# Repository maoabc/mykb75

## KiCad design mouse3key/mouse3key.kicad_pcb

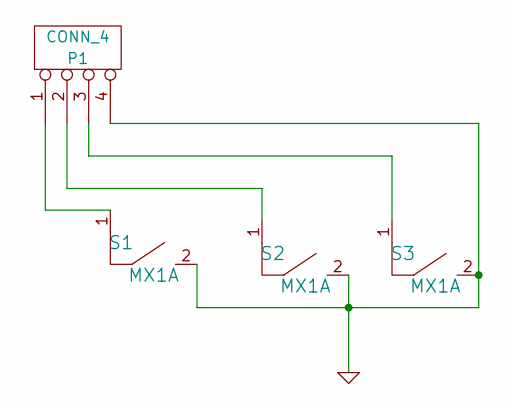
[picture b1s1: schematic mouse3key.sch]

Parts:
P1: CONN_4; connector-ffc-4p
S1, S2, S3: MX1A

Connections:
GND: P1.4, S1.2, S2.2, S3.2
unnamed: P1.1, S1.1
unnamed: P1.2, S2.1
unnamed: P1.3, S3.1

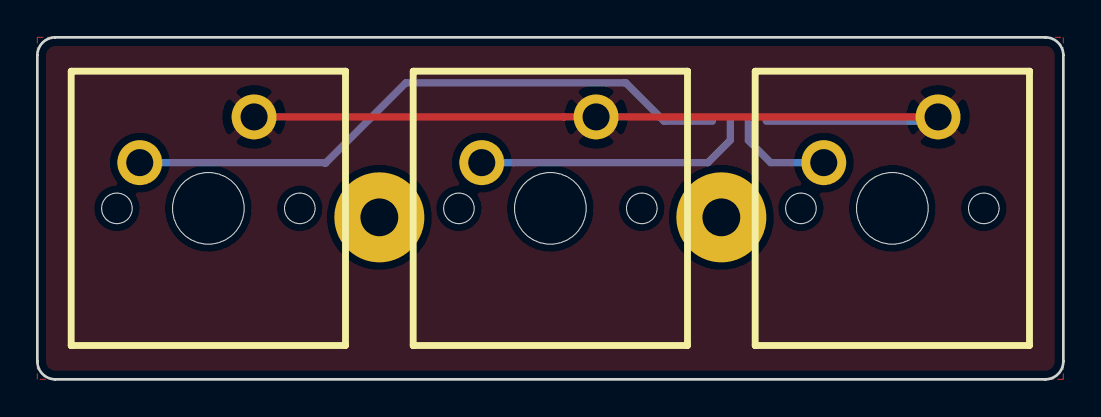
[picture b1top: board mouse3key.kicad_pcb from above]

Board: 2 copper layers, 57.0 x 19.0 mm, 6 parts (1 on the bottom side), 4 nets.

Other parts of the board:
HOLE: VAL**; M2
HOLE#2: VAL**; M2

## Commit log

2018-01-09 修改usb接口为type c
2018-01-20 增加一列F功能区 增加TrackPiont模块,同时增加ffc排线接口 右移右侧键布局
2018-02-01 第一版 修改了鼠标三键错位 TrackPiont模块ffc接口位置修改方便连接
2023-03-24 一些改动
